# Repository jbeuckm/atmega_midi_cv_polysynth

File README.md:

atmega_midi_cv_polysynth
========================

(This is a new clone of my monosynth MIDI>CV that will be modified for polyphonic productions.)

Uses the Arduino MIDI library to operate four x MCP4822 12-bit DAC with internal voltage reference.

Largely based on http://www.experimentalistsanonymous.com/ve3wwg/doku.php?id=analog_synth_midi

Uses 4922 library from http://www.alhin.de/arduino

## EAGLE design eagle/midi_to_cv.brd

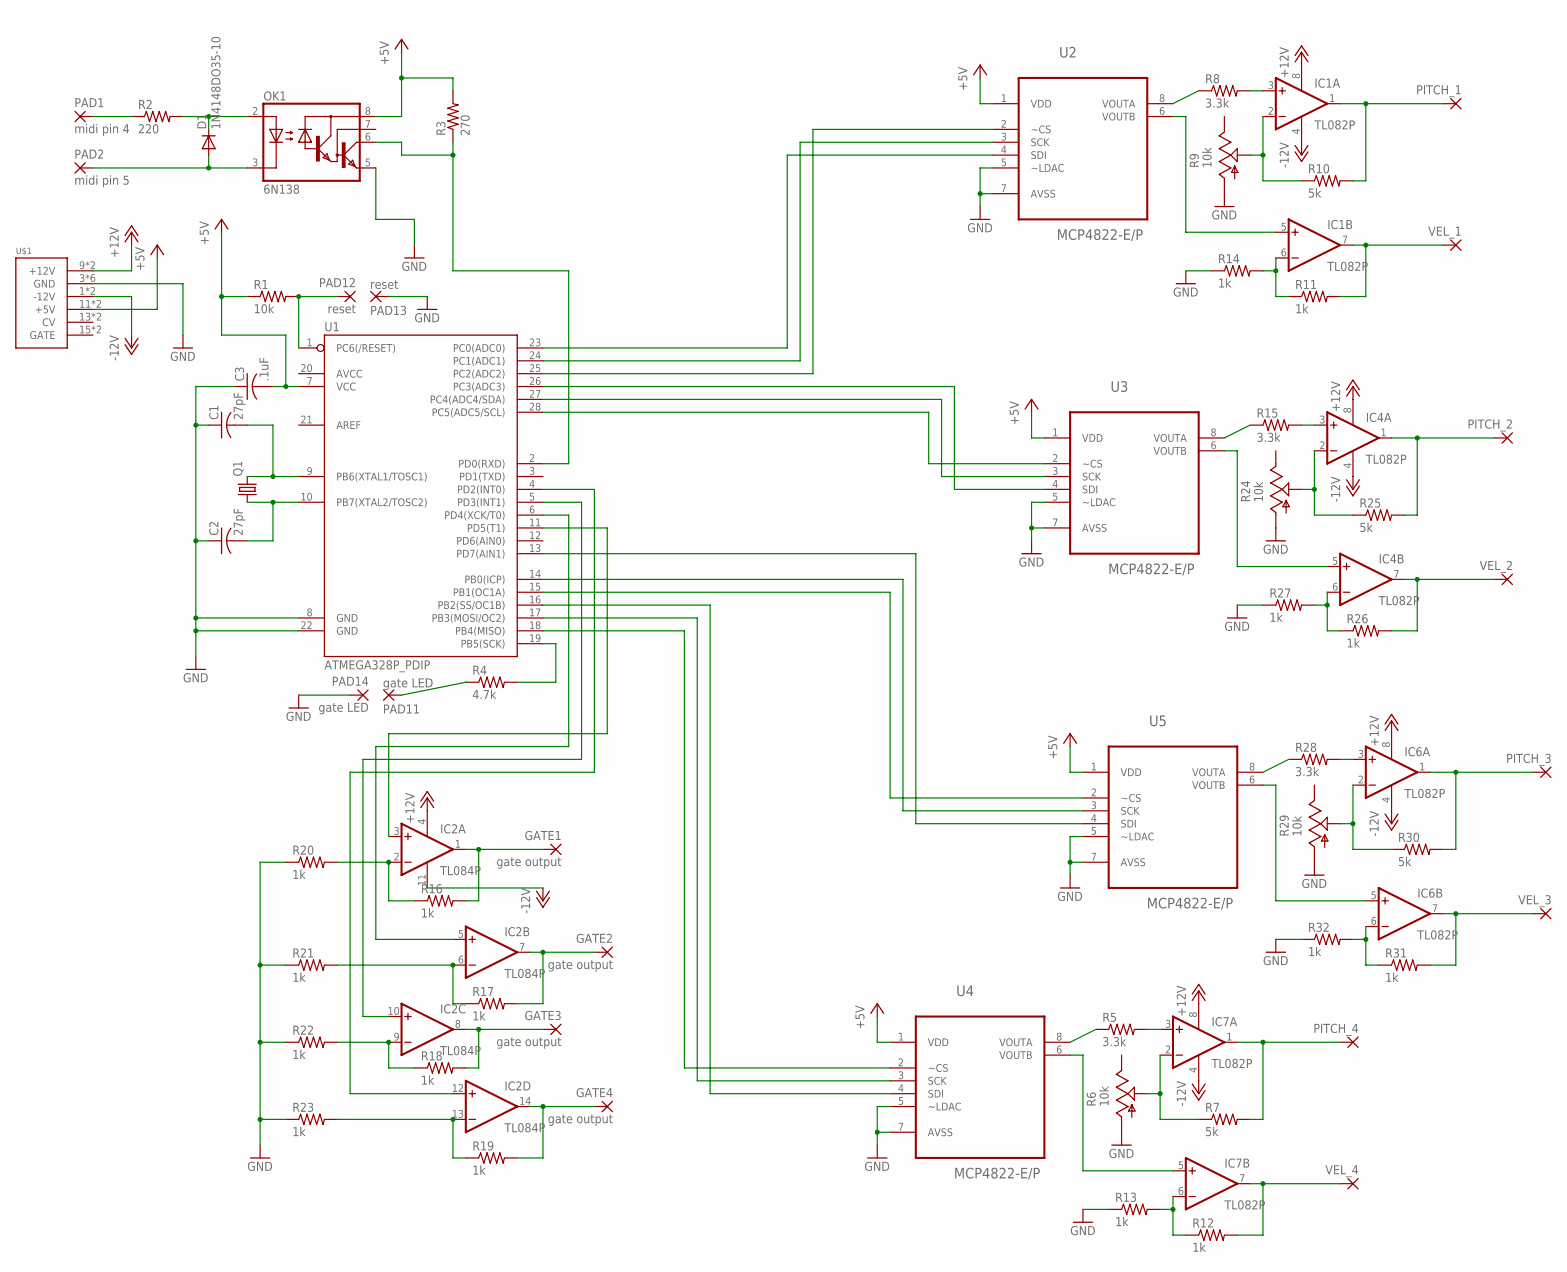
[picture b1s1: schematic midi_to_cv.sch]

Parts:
C1, C2: 27pF; C025-040X050
C3: .1uF; C025-040X050
D1: 1N4148DO35-10; DO35-10
GATE1, GATE2, GATE3, GATE4: gate output; 2,54/0,9
IC1, IC4, IC6, IC7: TL082P; DIL08
IC2: TL084P; DIL14
OK1: 6N138; DIL08
PAD1: midi pin 4; 2,54/0,9
PAD2: midi pin 5; 2,54/0,9
PAD11, PAD14: gate LED; 2,54/0,9
PAD12, PAD13: reset; 2,54/0,9
PITCH_1, PITCH_2, PITCH_3, PITCH_4: 2,54/0,9
Q1: CRYSTALHC49U-V; HC49U-V
R1: 10k; 0207/10
R2: 220; 0207/10
R3: 270; 0207/10
R4: 4.7k; 0207/10
R5, R8, R15, R28: 3.3k; 0207/10
R6, R9, R24, R29: 10k; B64W
R7, R10, R25, R30: 5k; 0207/10
R11, R12, R13, R14, R16, R17, R18, R19, R20, R21, R22, R23, R26, R27, R31, R32: 1k; 0207/10
U1: ATMEGA328P_PDIP; DIL28-3
U2, U3, U4, U5: MCP4822-E/P; DIP254P762X432-8
U$1: POWER; POWER_16
VEL_1, VEL_2, VEL_3, VEL_4: 2,54/0,9

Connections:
+5V: C3.2, OK1.8 (VCC), R1.1, R3.2, U1.7 (VCC), U2.1 (VDD), U3.1 (VDD), U4.1 (VDD), U5.1 (VDD), U$1.11 (+5V), U$1.12 (+5V)
+12V: IC1.8 (V+), IC2.4 (V+), IC4.8 (V+), IC6.8 (V+), IC7.8 (V+), U$1.9 (+12V), U$1.10 (+12V)
-12V: IC1.4 (V-), IC2.11 (V-), IC4.4 (V-), IC6.4 (V-), IC7.4 (V-), U$1.1 (-12V), U$1.2 (-12V)
GND: C1.1, C2.1, C3.1, OK1.5 (GND), PAD13.1, PAD14.1, R6.A, R9.A, R13.1, R14.1, R20.1, R21.1, R22.1, R23.1, R24.A, R27.1, R29.A, R32.1, U1.8 (GND), U1.22 (GND), U2.5 (~LDAC), U2.7 (AVSS), U3.5 (~LDAC), U3.7 (AVSS), U4.5 (~LDAC), U4.7 (AVSS), U5.5 (~LDAC), U5.7 (AVSS), U$1.3 (GND), U$1.4 (GND), U$1.5 (GND), U$1.6 (GND), U$1.7 (GND), U$1.8 (GND)
unnamed: PAD12.1, R1.2, U1.1 (PC6(/RESET))
unnamed: R5.1, U4.8 (VOUTA)
unnamed: D1.A, OK1.3 (C), PAD2.1
unnamed: C1.2, Q1.2, U1.9 (PB6(XTAL1/TOSC1))
unnamed: C2.2, Q1.1, U1.10 (PB7(XTAL2/TOSC2))
unnamed: IC7.3 (+IN), R5.2
unnamed: D1.C, OK1.2 (A), R2.2
unnamed: PAD1.1, R2.1
unnamed: IC7.1 (OUT), PITCH_4.1, R7.2
unnamed: R4.2, U1.19 (PB5(SCK))
unnamed: PAD11.1, R4.1
unnamed: IC7.2 (-IN), R6.S, R7.1
unnamed: R8.1, U2.8 (VOUTA)
unnamed: U1.17 (PB3(MOSI/OC2)), U4.3 (SCK)
unnamed: U1.16 (PB2(SS/OC1B)), U4.4 (SDI)
unnamed: IC1.3 (+IN), R8.2
unnamed: IC1.1 (OUT), PITCH_1.1, R10.2
unnamed: IC1.2 (-IN), R9.S, R10.1
unnamed: IC7.7 (OUT), R12.2, VEL_4.1
unnamed: IC7.6 (-IN), R12.1, R13.2
unnamed: IC1.7 (OUT), R11.2, VEL_1.1
unnamed: IC1.6 (-IN), R11.1, R14.2
unnamed: IC1.5 (+IN), U2.6 (VOUTB)
unnamed: R15.1, U3.8 (VOUTA)
unnamed: IC4.3 (+IN), R15.2
unnamed: U1.18 (PB4(MISO)), U4.2 (~CS)
unnamed: U1.13 (PD7(AIN1)), U5.4 (SDI)
unnamed: U1.15 (PB1(OC1A)), U5.2 (~CS)
unnamed: OK1.6 (VO), R3.1, U1.2 (PD0(RXD))
unnamed: IC2.3 (+IN), U1.11 (PD5(T1))
unnamed: IC2.5 (+IN), U1.6 (PD4(XCK/T0))
unnamed: GATE1.1, IC2.1 (OUT), R16.2
unnamed: GATE2.1, IC2.7 (OUT), R17.2
unnamed: GATE3.1, IC2.8 (OUT), R18.2
unnamed: GATE4.1, IC2.14 (OUT), R19.2
unnamed: IC2.2 (-IN), R16.1, R20.2
unnamed: IC2.13 (-IN), R19.1, R23.2
unnamed: IC2.9 (-IN), R18.1, R22.2
unnamed: IC2.6 (-IN), R17.1, R21.2
unnamed: IC2.10 (+IN), U1.5 (PD3(INT1))
unnamed: IC2.12 (+IN), U1.4 (PD2(INT0))
unnamed: IC4.1 (OUT), PITCH_2.1, R25.2
unnamed: IC4.2 (-IN), R24.S, R25.1
unnamed: IC7.5 (+IN), U4.6 (VOUTB)
unnamed: IC4.7 (OUT), R26.2, VEL_2.1
unnamed: IC4.6 (-IN), R26.1, R27.2
unnamed: IC4.5 (+IN), U3.6 (VOUTB)
unnamed: R28.1, U5.8 (VOUTA)
unnamed: IC6.3 (+IN), R28.2
unnamed: IC6.1 (OUT), PITCH_3.1, R30.2
unnamed: IC6.2 (-IN), R29.S, R30.1
unnamed: IC6.7 (OUT), R31.2, VEL_3.1
unnamed: IC6.6 (-IN), R31.1, R32.2
unnamed: IC6.5 (+IN), U5.6 (VOUTB)
unnamed: U1.23 (PC0(ADC0)), U2.4 (SDI)
unnamed: U1.24 (PC1(ADC1)), U2.3 (SCK)
unnamed: U1.25 (PC2(ADC2)), U2.2 (~CS)
unnamed: U1.26 (PC3(ADC3)), U3.4 (SDI)
unnamed: U1.27 (PC4(ADC4/SDA)), U3.3 (SCK)
unnamed: U1.28 (PC5(ADC5/SCL)), U3.2 (~CS)
unnamed: U1.14 (PB0(ICP)), U5.3 (SCK)

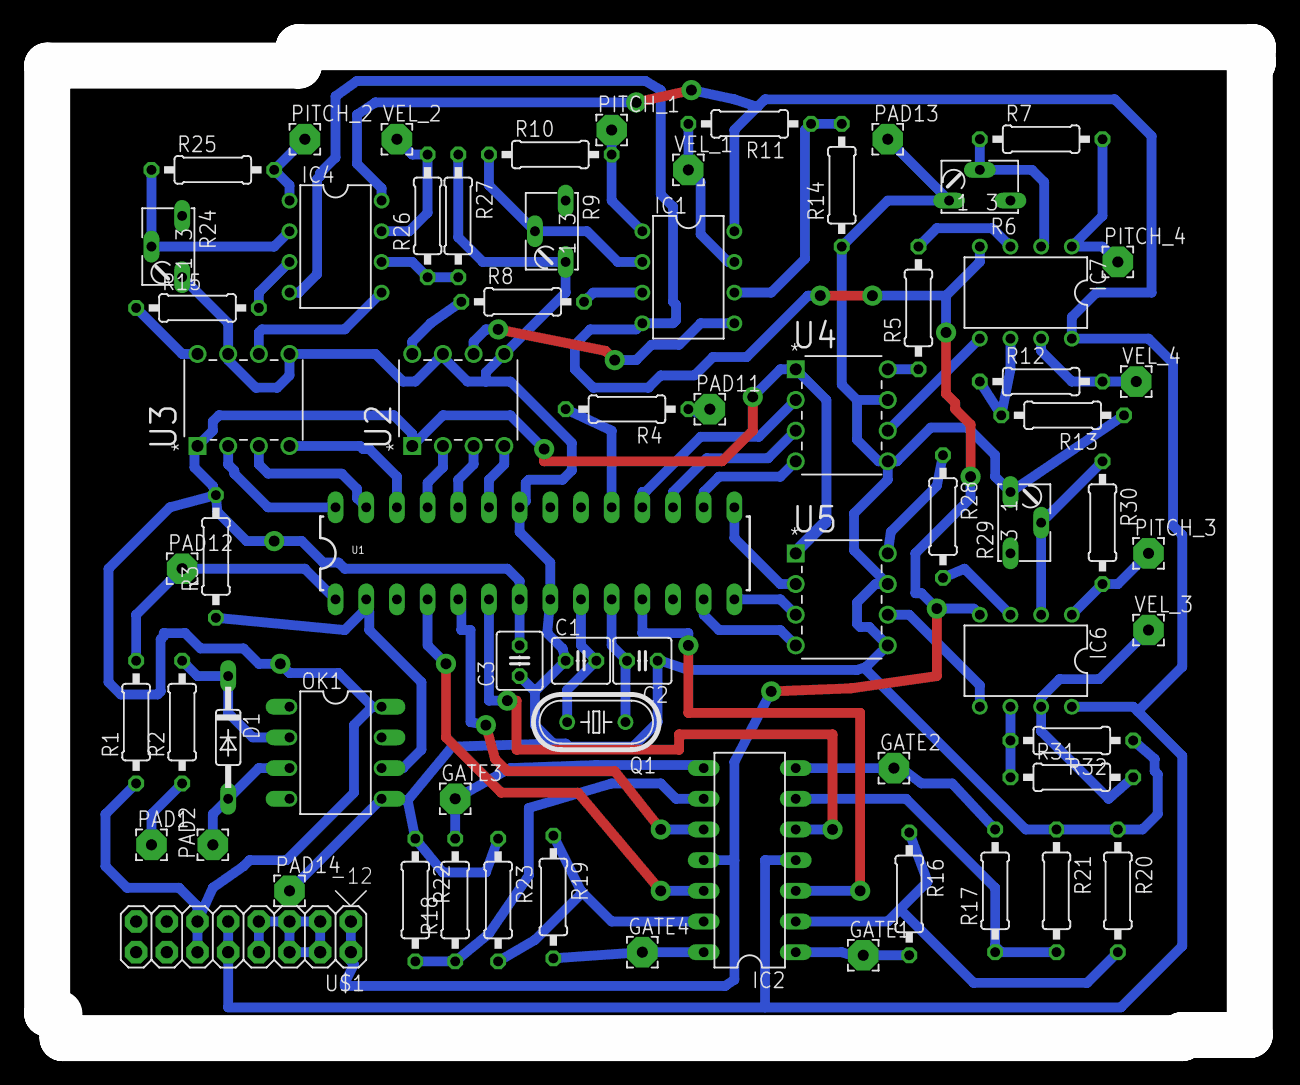
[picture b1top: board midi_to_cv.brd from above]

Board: 2 copper layers, 100.1 x 82.0 mm, 67 parts (0 on the bottom side), 65 nets.

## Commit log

2014-12-19 initial commit of cloned repo
2014-12-21 converting to poly4
2014-12-21 replicated pitch and velocity outputs four times
2014-12-21 connected the dacs
2014-12-21 prettied up the schematic
2014-12-21 renumbered op amps
2014-12-21 draft of the software
2014-12-21 code cleaned up
2014-12-22 moved parts onto board area
2014-12-23 working to route the board
2014-12-23 swapped dac control lines and need to do so in software
2014-12-23 nearly routable
2014-12-24 hand routing
2014-12-24 manually routed and vias adjusted
2014-12-25 will route gates to op amps instead of jumper pads
2014-12-25 routed with vias to gates
2015-01-05 corrected dac com lines for the updated schematic and things work
2015-01-09 updated panel for polysynth
2015-03-18 updated arduino code
2015-03-18 attempt to retain notes until no voice is left
2015-03-19 note selection works as intended
2015-03-19 including mcp4922 library with delay modified to delayMicroseconds

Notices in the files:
parts and their libraries:
SparkFun-DigitalIC: Licensing: Creative Commons ShareAlike 4.0 International - https://creativecommons.org/licenses/by-sa/4.0
